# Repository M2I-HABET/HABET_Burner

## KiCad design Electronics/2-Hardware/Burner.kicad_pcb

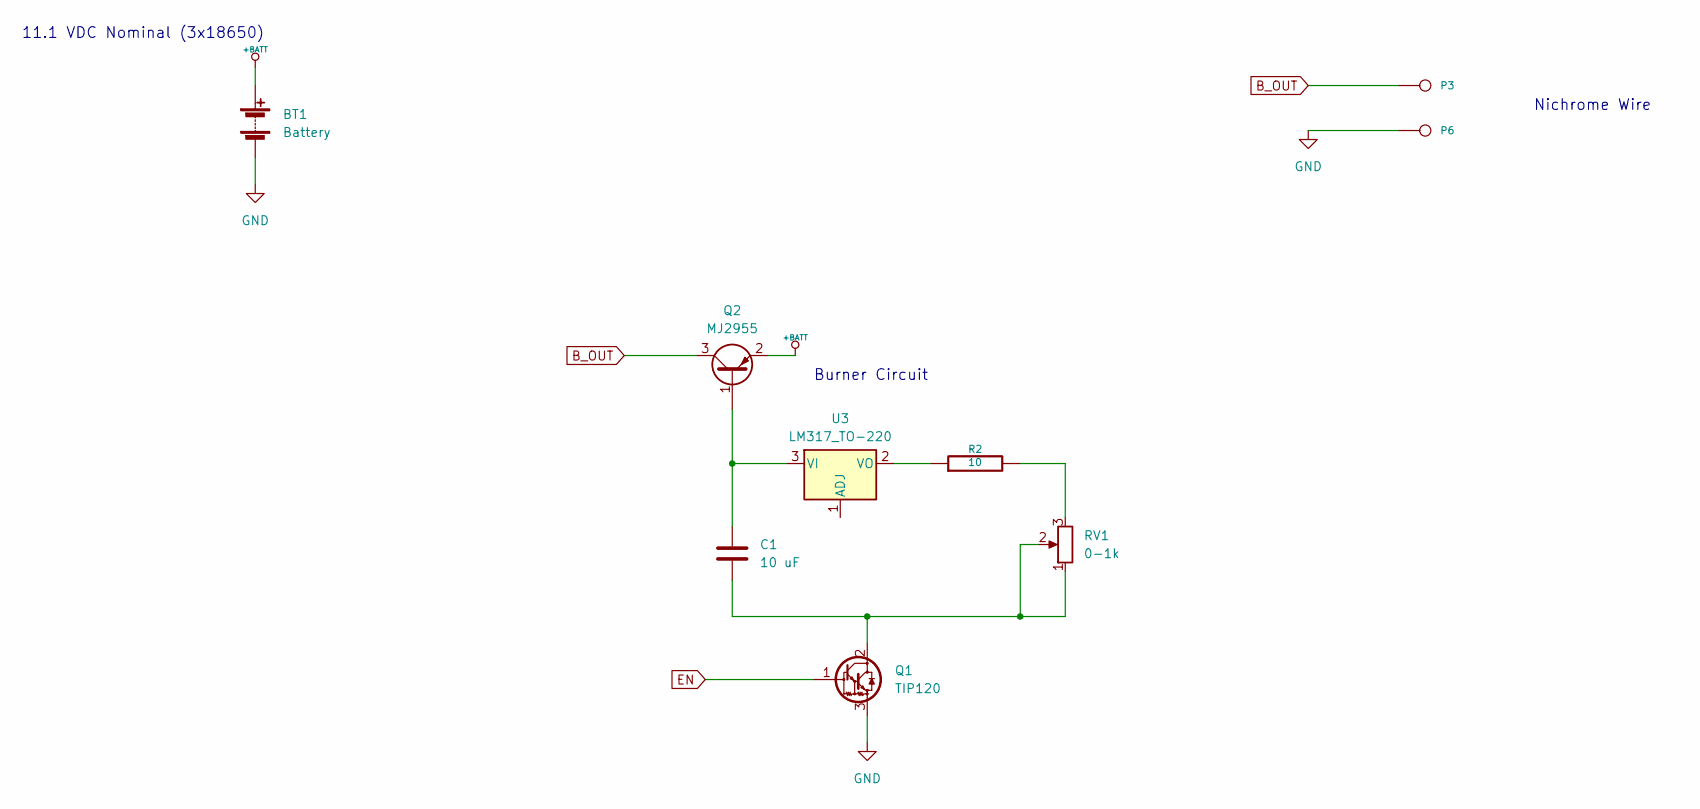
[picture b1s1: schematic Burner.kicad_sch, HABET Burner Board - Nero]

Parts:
BT1: Battery; BatteryHolder_Keystone_1042_1x18650
C1: 10 uF; CP_Axial_L10.0mm_D4.5mm_P15.00mm_Horizontal
P3, P6: CONN_1; Pin_D0.7mm_L6.5mm_W1.8mm_FlatFork
Q1: TIP120; TO-220-3_Vertical
Q2: MJ2955; TO-3
R2: 10; R_Axial_DIN0411_L9.9mm_D3.6mm_P25.40mm_Horizontal; DigikeyPart RHM2.7BGCT-ND
RV1: 0-1k; Potentiometer_Bourns_3339S_Horizontal
U3: LM317_TO-220; TO-220-3_Vertical

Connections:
+BATT: BT1.1 (+), Q2.2 (E)
B_OUT: P3.1, Q2.3 (C)
EN: Q1.1 (B)
GND: BT1.2 (-), P6.1, Q1.3 (E)
unnamed: C1.2, Q1.2 (C), RV1.1, RV1.2
unnamed: C1.1, Q2.1 (B), U3.3 (VI)
unnamed: R2.2, RV1.3
unnamed: R2.1, U3.2 (VO)

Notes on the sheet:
Nichrome Wire
11.1 VDC Nominal (3x18650)
Burner Circuit

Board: 2 copper layers, 9 parts (0 on the bottom side), 7 nets, no tracks yet.

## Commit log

2023-07-08 Initial Schematic redo
2023-08-01 Update to KiCad
2023-10-17 F23 update to burner
2023-11-15 Create placeholder
